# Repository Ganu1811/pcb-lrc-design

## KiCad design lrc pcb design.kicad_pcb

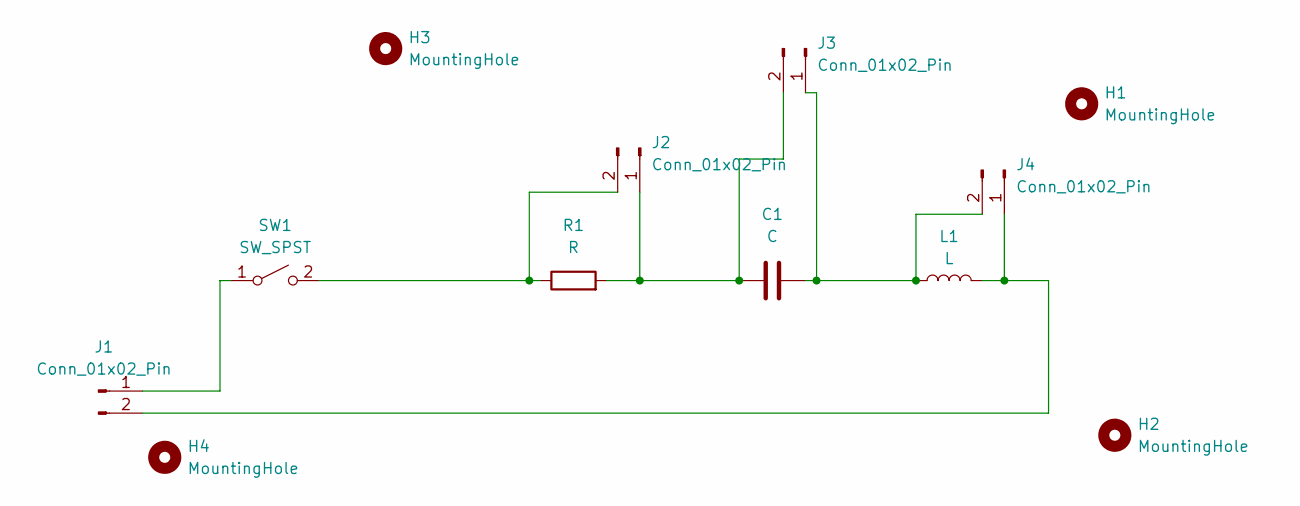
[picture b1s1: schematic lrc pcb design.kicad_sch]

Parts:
C1: C; CP_Axial_L11.0mm_D6.0mm_P18.00mm_Horizontal
H1, H2, H3, H4: MountingHole; MountingHole_2.2mm_M2
J1, J2, J3, J4: Conn_01x02_Pin; PinHeader_1x02_P2.54mm_Vertical
L1: L; L_Axial_L6.6mm_D2.7mm_P2.54mm_Vertical_Vishay_IM-2
R1: R; R_Axial_DIN0204_L3.6mm_D1.6mm_P5.08mm_Horizontal
SW1: SW_SPST; SW_DIP_SPSTx01_Piano_10.8x4.1mm_W7.62mm_P2.54mm

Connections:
unnamed: J1.1, SW1.1 (A)
unnamed: J1.2, J4.1, L1.2
unnamed: C1.1, J2.1, J3.2, R1.2
unnamed: J2.2, R1.1, SW1.2 (B)
unnamed: C1.2, J3.1, J4.2, L1.1

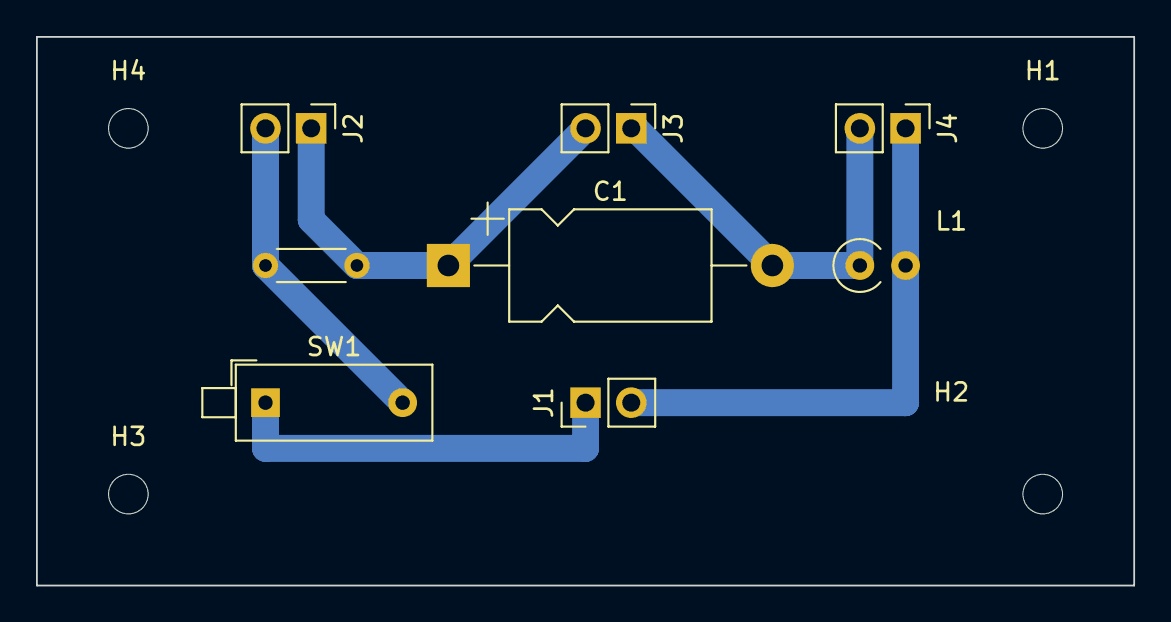
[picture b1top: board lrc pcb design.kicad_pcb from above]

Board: 2 copper layers, 61.0 x 30.5 mm, 12 parts (0 on the bottom side), 5 nets.
